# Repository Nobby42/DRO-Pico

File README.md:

# 4 Channel DRO with Raspberry Pico RP2040

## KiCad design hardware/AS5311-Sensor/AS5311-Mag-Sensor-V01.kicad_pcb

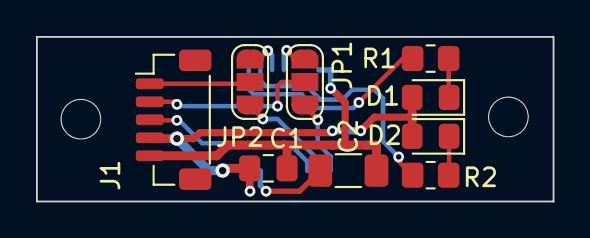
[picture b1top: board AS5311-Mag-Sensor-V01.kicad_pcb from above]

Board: 2 copper layers, 28.7 x 9.1 mm, 10 parts (1 on the bottom side), 14 nets.

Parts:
C1: 100n; C_0805_2012Metric_Pad1.18x1.45mm_HandSolder
C2: 4,7u; C_1206_3216Metric_Pad1.33x1.80mm_HandSolder
D1: LED gr; LED_0805_2012Metric_Pad1.15x1.40mm_HandSolder
D2: LED rt; LED_0805_2012Metric_Pad1.15x1.40mm_HandSolder
J1: Conn_01x05_Pin; JST_SH_BM05B-SRSS-TB_1x05-1MP_P1.00mm_Vertical
JP1, JP2: SolderJumper-3_P1.3mm_Open_RoundedPad1.0x1.5mm_NumberLabels
R1, R2: 1k; R_0805_2012Metric_Pad1.20x1.40mm_HandSolder
U1: AS5311; TSSOP20_AS5311-ATST-500_AMS-L

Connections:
+5V: C1.1, D1.2 (A), D2.2 (A), J1.4, U1.19 (VDD5V)
GND: C1.2, C2.2, J1.5, U1.8 (VSS), U1.9 (PROG)
unnamed: D1.1 (K), R1.2
unnamed: D2.1 (K), R2.1
unnamed: J1.1, JP2.2 (C)
unnamed: J1.2, JP1.2 (C)
unnamed: J1.3, U1.14 (CSN)
unnamed: JP1.1 (A), U1.12 (DO)
unnamed: JP1.3 (B), U1.5 (B)
unnamed: JP2.1 (A), U1.13 (CLK)
unnamed: JP2.3 (B), U1.4 (A)
unnamed: R2.2, U1.3 (MAGDECN)
unnamed: R1.1, U1.2 (MAGINCN)
unnamed: C2.1, U1.18 (VDD3V3)

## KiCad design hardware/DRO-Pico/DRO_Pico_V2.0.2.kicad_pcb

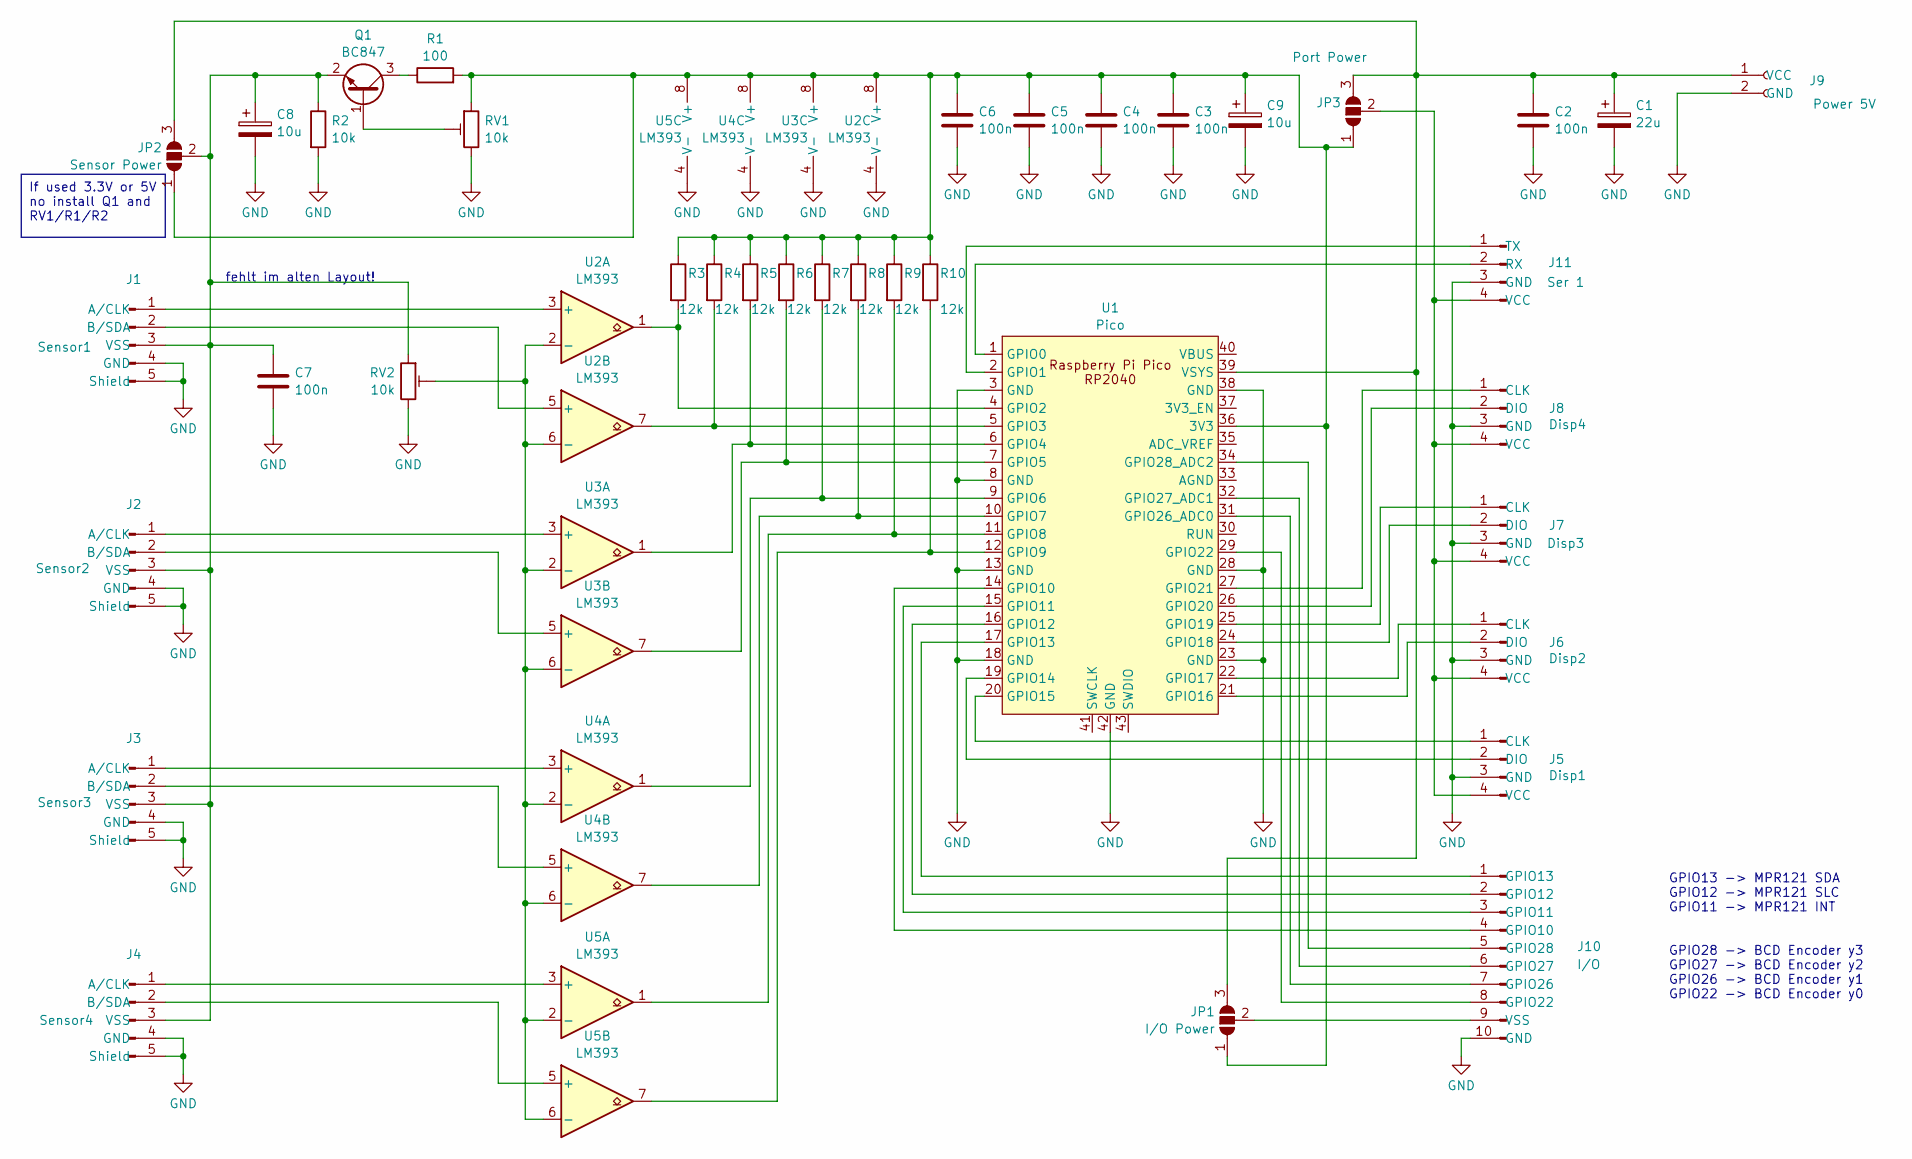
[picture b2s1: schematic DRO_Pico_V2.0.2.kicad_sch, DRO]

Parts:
C1: 22u; C_1812_4532Metric
C2, C3, C4, C5, C6, C7: 100n; C_1206_3216Metric
C8, C9: 10u; C_1206_3216Metric_Pad1.33x1.80mm_HandSolder
J1: Sensor1; JST_EH_B5B-EH-A_1x05_P2.50mm_Vertical
J2: Sensor2; JST_EH_B5B-EH-A_1x05_P2.50mm_Vertical
J3: Sensor3; JST_EH_B5B-EH-A_1x05_P2.50mm_Vertical
J4: Sensor4; JST_EH_B5B-EH-A_1x05_P2.50mm_Vertical
J5: Disp1; JST_EH_B4B-EH-A_1x04_P2.50mm_Vertical
J6: Disp2; JST_EH_B4B-EH-A_1x04_P2.50mm_Vertical
J7: Disp3; JST_EH_B4B-EH-A_1x04_P2.50mm_Vertical
J8: Disp4; JST_EH_B4B-EH-A_1x04_P2.50mm_Vertical
J9: Power 5V; TerminalBlock_bornier-2_P5.08mm
J10: I/O; JST_EH_B10B-EH-A_1x10_P2.50mm_Vertical
J11: Ser 1; JST_EH_B4B-EH-A_1x04_P2.50mm_Vertical
JP1: I/O Power; SolderJumper-3_P1.3mm_Open_RoundedPad1.0x1.5mm_NumberLabels
JP2: Sensor Power; SolderJumper-3_P1.3mm_Open_RoundedPad1.0x1.5mm_NumberLabels
JP3: Port Power; SolderJumper-3_P1.3mm_Open_RoundedPad1.0x1.5mm_NumberLabels
Q1: BC847; SOT-23
R1: 100; R_0805_2012Metric
R2: 10k; R_0805_2012Metric
R3, R4, R5, R6, R7, R8, R9, R10: 12k; R_0805_2012Metric
RV1, RV2: 10k; Potentiometer_ACP_CA6-H2,5_Horizontal
U1: Pico; RPi_Pico_SMD_TH
U2, U3, U4, U5: LM393; SO-8_3.9x4.9mm_P1.27mm

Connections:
GND: C1.2, C2.2, C3.2, C4.2, C5.2, C6.2, C7.2, C8.2, C9.2, J1.4 (GND), J1.5 (Shield), J2.4 (GND), J2.5 (Shield), J3.4 (GND), J3.5 (Shield), J4.4 (GND), J4.5 (Shield), J5.3 (GND), J6.3 (GND), J7.3 (GND), J8.3 (GND), J9.2 (GND), J10.10 (GND), J11.3 (GND), R2.2, RV1.3, RV2.3, U1.3 (GND), U1.8 (GND), U1.13 (GND), U1.18 (GND), U1.23 (GND), U1.28 (GND), U1.38 (GND), U1.42 (GND), U2.4 (V-), U3.4 (V-), U4.4 (V-), U5.4 (V-)
unnamed: J1.1 (CLK), U2.3 (+)
unnamed: J1.2 (SDA), U2.5 (+)
unnamed: C7.1, C8.1, J1.3 (VSS), J2.3 (VSS), J3.3 (VSS), J4.3 (VSS), JP2.2 (C), Q1.2 (E), R2.1, RV2.1
unnamed: J2.1 (CLK), U3.3 (+)
unnamed: J2.2 (SDA), U3.5 (+)
unnamed: J3.1 (CLK), U4.3 (+)
unnamed: J3.2 (SDA), U4.5 (+)
unnamed: J4.1 (CLK), U5.3 (+)
unnamed: J4.2 (SDA), U5.5 (+)
unnamed: J5.1 (CLK), U1.20 (GPIO15)
unnamed: J5.2 (DIO), U1.19 (GPIO14)
unnamed: J6.1 (CLK), U1.22 (GPIO17)
unnamed: J6.2 (DIO), U1.21 (GPIO16)
unnamed: J7.1 (CLK), U1.25 (GPIO19)
unnamed: J7.2 (DIO), U1.24 (GPIO18)
unnamed: J8.1 (CLK), U1.27 (GPIO21)
unnamed: J8.2 (DIO), U1.26 (GPIO20)
unnamed: C1.1, C2.1, J9.1 (VCC), JP1.3 (B), JP2.3 (B), JP3.3 (B), U1.39 (VSYS)
unnamed: J10.4 (GPIO10), U1.14 (GPIO10)
unnamed: J10.3 (GPIO11), U1.15 (GPIO11)
unnamed: J10.2 (GPIO12), U1.16 (GPIO12)
unnamed: J10.1 (GPIO13), U1.17 (GPIO13)
unnamed: J10.8 (GPIO22), U1.29 (GPIO22)
unnamed: J10.7 (GPIO26), U1.31 (GPIO26_ADC0)
unnamed: J10.6 (GPIO27), U1.32 (GPIO27_ADC1)
unnamed: J10.5 (GPIO28), U1.34 (GPIO28_ADC2)
unnamed: J10.9 (VSS), JP1.2 (C)
unnamed: J11.2 (RX), U1.1 (GPIO0)
unnamed: J11.1 (TX), U1.2 (GPIO1)
unnamed: J5.4 (VCC), J6.4 (VCC), J7.4 (VCC), J8.4 (VCC), J11.4 (VCC), JP3.2 (C)
unnamed: C3.1, C4.1, C5.1, C6.1, C9.1, JP1.1 (A), JP2.1 (A), JP3.1 (A), R1.2, R3.1, R4.1, R5.1, R6.1, R7.1, R8.1, R9.1, R10.1, RV1.1, U1.36 (3V3), U2.8 (V+), U3.8 (V+), U4.8 (V+), U5.8 (V+)
unnamed: Q1.1 (B), RV1.2
unnamed: Q1.3 (C), R1.1
unnamed: R3.2, U1.4 (GPIO2), U2.1
unnamed: R4.2, U1.5 (GPIO3), U2.7
unnamed: R5.2, U1.6 (GPIO4), U3.1
unnamed: R6.2, U1.7 (GPIO5), U3.7
unnamed: R7.2, U1.9 (GPIO6), U4.1
unnamed: R8.2, U1.10 (GPIO7), U4.7
unnamed: R9.2, U1.11 (GPIO8), U5.1
unnamed: R10.2, U1.12 (GPIO9), U5.7
unnamed: RV2.2, U2.2 (-), U2.6 (-), U3.2 (-), U3.6 (-), U4.2 (-), U4.6 (-), U5.2 (-), U5.6 (-)

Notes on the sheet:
If used 3.3V or 5V no install Q1 and RV1/R1/R2
GPIO13 -> MPR121 SDA GPIO12 -> MPR121 SLC GPIO11 -> MPR121 INT GPIO28 -> BCD Encoder y3 GPIO27 -> BCD Encoder y2 GPIO26 -> BCD Encoder y1 GPIO22 -> BCD Encoder y0
fehlt im alten Layout!

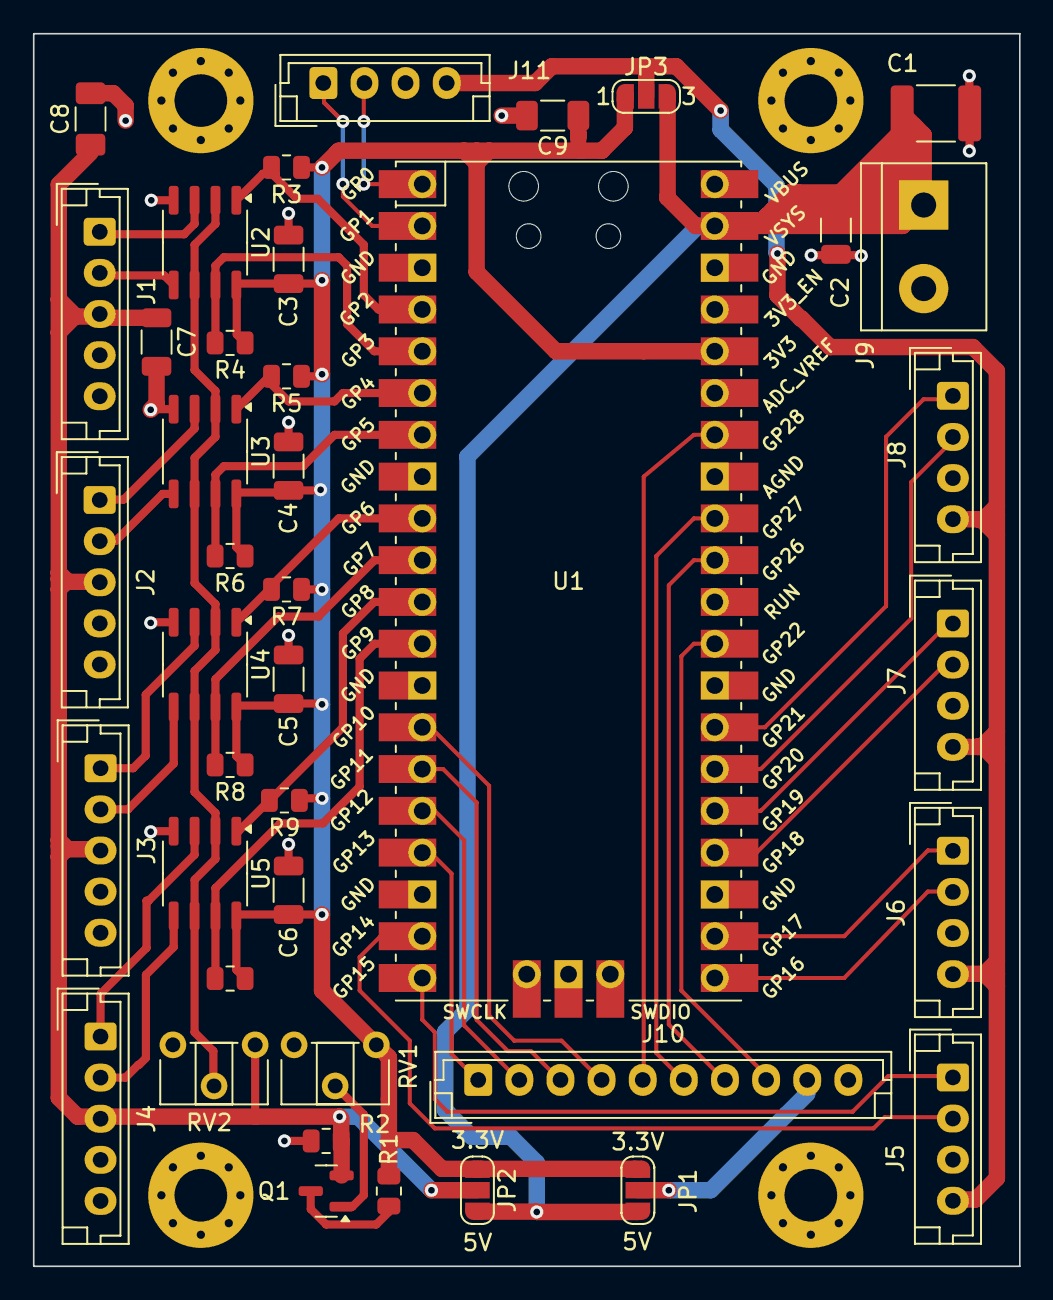
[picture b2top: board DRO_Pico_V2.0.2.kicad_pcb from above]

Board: 2 copper layers, 59.9 x 74.9 mm, 41 parts (0 on the bottom side), 43 nets.

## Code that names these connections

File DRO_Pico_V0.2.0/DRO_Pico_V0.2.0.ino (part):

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
/*
Change for I2C in pins_arduino.h for Raspberry PICO (in Mac: Users/xxxxx/Library/Arduino15/packages/arduino/hardware/mbed_rp2040/x.x.x/variants/RASPBERRY_PI_PICO/pins_arduino.h)
in the wire section the I2C Pins in which you use. Default is GPIO4 and GPIO5

// Wire
#define PIN_WIRE_SDA        (12u) -> Pin GPIO12
#define PIN_WIRE_SCL        (13u) -> Pin GPIO13

*/#define MPR_ADD 0x5A // I2C Adress MPR121

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
NeoPixelConnect p(0, MAXIMUM_NUM_NEOPIXELS, pio1, 1);

PioEncoder encoderZ0(2); // encoder is connected to GPIO2 and GPIO3
PioEncoder encoderZ1(4); // encoder is connected to GPIO4 and GPIO5
PioEncoder encoderX(6);  // encoder is connected to GPIO6 and GPIO7
PioEncoder encoderZR(8); // encoder is connected to GPIO8 and GPIO9
// Module TM1637 connection pins (Digital Pins)
// TM1637TinyDisplay display(CLK, DIO);
TM1637TinyDisplay6 displayZ0(21,20);
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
